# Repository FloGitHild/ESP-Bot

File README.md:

# ESP32-Kettenroboter

Ein modularer Kettenroboter als MINT-Lernprojekt: Schülerinnen und Schüler
sollen Aufbau, Sensorik und Programmierung eines mobilen Roboters kennenlernen.
Das Projekt verbindet ein Robotik-Konzept mit KiCad-Entwürfen und ersten
Arduino-Testprogrammen.

> **Projektstand:** Dieses Repository dokumentiert ein Konzept und begonnene
> Hardware-Entwicklung. Die beschriebenen Funktionen sind nicht automatisch
> als fertig aufgebaut, vollständig programmiert oder praktisch validiert zu
> verstehen. Insbesondere ist hier noch keine vollständige Fahr- und
> Autonomiesoftware enthalten.

## Konzept

Der geplante Roboter soll Hindernisse erkennen, Linien verfolgen, Abstände und
Fahrdaten erfassen und Daten per WLAN weitergeben. Das Konzept sieht vor, bis zu
20 möglichst gleiche Einheiten für den MINT-Unterricht aufzubauen.

Wesentliche Bausteine der beschriebenen Architektur:

- **Zwei Controller:** Ein ESP32-WROOM-32E übernimmt die übergeordnete Logik,
  Sensorik und WLAN-Kommunikation. Ein Arduino Pro Micro ist für zeitkritische
  Motorsteuerung, Encoder und Signaltöne vorgesehen.
- **Kettenantrieb:** Zwei N20-Getriebemotoren mit Encodern werden über einen
  Motortreiber angesteuert.
- **Sensorik:** Ein HC-SR04 für die Hinderniserkennung vorn, zwei VL53L0X für
  seitliche Abstandsmessung, ein TCS34725 für die Linienerkennung und eine
  LSM6DSOX-IMU für Beschleunigungs- und Drehratenmessung.
- **Erweiterbarer I²C-Bus:** Ein TCA/PCA9548A-Multiplexer soll Sensoren mit
  gleicher I²C-Adresse voneinander trennen. Ein zusätzlicher Anschluss am
  Gehäusedeckel ist für externe I²C-Module vorgesehen.
- **Rückmeldung und Aufzeichnung:** OLED, WS2812-LEDs und Piezo dienen der
  Ausgabe; eine microSD-Karte ist für Sensor- und Fahrdaten vorgesehen.
- **Energieversorgung:** Das Konzept beschreibt einen 1S-LiPo-Akku mit
  getrennten Boost-Versorgungen für Motoren und Logik.

Die detaillierte Beschreibung, Pin- und Busbelegungen, Stückliste sowie
Kostenschätzungen stehen in den Konzeptunterlagen. Werte daraus sind
Planungsangaben und müssen vor dem Aufbau anhand der verwendeten Bauteile
überprüft werden.

## Inhalt des Repositorys

| Pfad | Inhalt |
| --- | --- |
| [`Kettenroboter_Konzept_V1.0.html`](Kettenroboter_Konzept_V1.0.html) | Ausführliche Konzeptbeschreibung mit Architektur, Sensorik, Versorgung, Pinplan und Kalkulation |
| [`Kettenroboter_Konzept_V1.0.docx`](Kettenroboter_Konzept_V1.0.docx) | Bearbeitbare Fassung des Konzepts |
| [`Kettenroboter - Konzept V1.0.pdf`](Kettenroboter%20-%20Konzept%20V1.0.pdf) | PDF-Fassung des Konzepts |
| [`KICAD/Platine_V1.0/`](KICAD/Platine_V1.0/) | KiCad-Schaltplan- und Platinenprojekt V1.0 |
| [`Arduino Codes/`](Arduino%20Codes/) | Arduino-Sketche für einzelne Hardwaretests |
| [`Datenblätter/`](Datenbl%C3%A4tter/) | Datenblätter und ESP32-Maßzeichnung |
| [`Teilliste.xlsx`](Teilliste.xlsx) | Bauteil- und Bestellübersicht |
| [`Neue Notiz 09-22-2026.pdf`](Neue%20Notiz%2009-22-2026.pdf) | Zusätzliche Projektnotiz |

## Arduino-Testsketche

Die Sketche testen einzelne Baugruppen und sind kein zusammenhängendes
Roboterprogramm:

| Sketch | Zweck |
| --- | --- |
| [`IIC_Bus_Scanner.ino`](Arduino%20Codes/IIC_Bus_Scanner/IIC_Bus_Scanner.ino) | Sucht I²C-Geräte direkt und an den Kanälen eines Multiplexers |
| [`IIC_MUX_Test.ino`](Arduino%20Codes/IIC_MUX_Test/IIC_MUX_Test.ino) | Prüft Multiplexer, Buspegel und Kanalwahl |
| [`MUX_Test.ino`](Arduino%20Codes/MUX_Test/MUX_Test.ino) | Weiterer Multiplexer-Test |
| [`OLED_Direct_Test.ino`](Arduino%20Codes/OLED_Direct_Test/OLED_Direct_Test.ino) | Initialisiert ein OLED und zeigt Beispieltexte an |

Die Sketche verwenden derzeit SDA an GPIO 15 und SCL an GPIO 16. Im
Konzept-Pinplan ist der I²C-Hauptbus dagegen auf GPIO 21/22 vorgesehen.
Vor dem Anschließen oder Ausführen daher die tatsächliche Verdrahtung, den
jeweiligen Sketch und den passenden ESP32-Pinplan miteinander abgleichen.
Der OLED-Test verwendet die Bibliothek **Adafruit_SSD1306**.

## Sicherheit und Prüfung

Der Entwurf umfasst einen Lithium-Polymer-Akku, Ladeelektronik, DC/DC-Wandler
und Motoren. Vor einem Aufbau oder Ladebetrieb müssen insbesondere Akku,
Ladeschaltung, Schutzfunktionen, Leitungsquerschnitte und Strombelastbarkeit
für die tatsächlich ausgewählten Komponenten geprüft werden. Lithium-Akkus
nicht unbeaufsichtigt oder entgegen den Herstellerangaben laden.

ESP32-GPIOs sind nicht 5-V-tolerant. Für den im Konzept vorgesehenen HC-SR04
muss insbesondere das Echo-Signal auf einen zulässigen ESP32-Pegel angepasst
werden. Maßgeblich sind die Datenblätter der konkret eingesetzten Bauteile.

## Urheberschaft und Nutzung

Die eigenen Projektideen, konzeptionellen Entscheidungen und Ausarbeitungen
dieses Projekts stammen von **Florian (GitHub: [FloGitHild](https://github.com/FloGitHild))**.
Sie dürfen nur verwendet, bearbeitet oder weiterverbreitet werden, wenn
**Florian (FloGitHild) klar als Urheber genannt wird**. Eine Nutzung ohne diese
Namensnennung ist nicht gestattet.

Die Namensnennung ist keine pauschale Lizenz für Inhalte Dritter. Datenblätter,
Herstellerangaben, Produktnamen und sonstige übernommene Materialien
unterliegen weiterhin den Rechten und Bedingungen ihrer jeweiligen
Rechteinhaber. Für solche Inhalte gelten die jeweiligen Lizenz- und
Nutzungsbedingungen.

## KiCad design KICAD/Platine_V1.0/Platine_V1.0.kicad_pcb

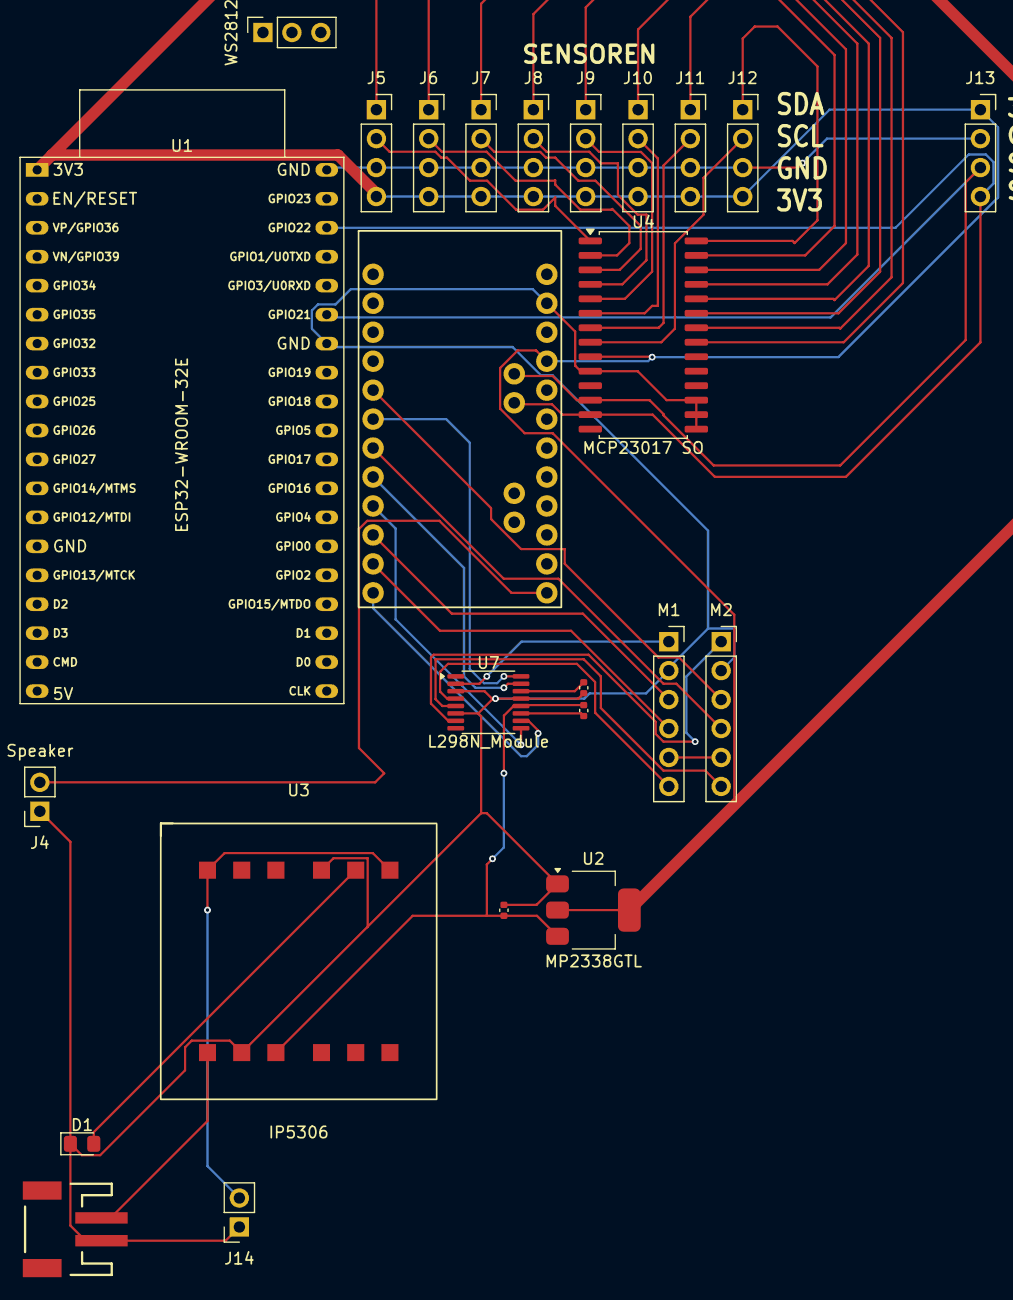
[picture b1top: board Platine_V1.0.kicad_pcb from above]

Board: 2 copper layers, 25 parts (0 on the bottom side), 40 nets.

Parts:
C1: 0.1uF; C_0402_1005Metric
C2: 2.2uF; C_0402_1005Metric
C3: 10uF; C_0402_1005Metric
D1: LED; LED_0805_2012Metric_Pad1.15x1.40mm_HandSolder
J1: JST_2mm_LiPo; JST_1x02_P2.0mm_Horizontal_SMD
J4: Speaker; PinSocket_1x02_P2.54mm_Vertical
J5, J6, J7, J8, J9, J10, J11, J12, J13: Conn_01x04_Socket; PinSocket_1x04_P2.54mm_Vertical
J14: Conn_01x02_Socket; PinSocket_1x02_P2.54mm_Vertical
M1, M2: Conn_01x06_Socket; PinSocket_1x06_P2.54mm_Vertical
U1: ESP32-WROOM-32E
U2: MP2338GTL; MP2338GTL_SOT23-5
U3: IP5306; IP5306_Module
U4: MCP23017 SO; L298N_Module
U5: Arduino Pro Mini; Arduino_Pro_Mini_Shield
U7: L298N_Module
WS2812: Conn_01x03_Socket; PinSocket_1x03_P2.54mm_Vertical

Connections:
unnamed: D1.2 (A), U3.5 (CHRG)
unnamed: C2.1, C3.1, D1.1 (K), J1.1 (-), J4.1, J5.3, J6.3, J7.3, J8.3, J9.3, J10.3, J11.3, J12.3, J13.2, J14.1, M1.2, M2.2, U1.14 (GND), U1.32 (GND), U1.38 (GND), U2.1 (GND), U3.4 (GND), U3.8 (BAT-), U4.10 (V_{SS}), U4.15 (A0), U4.16 (A1), U4.17 (A2), U5.23 (GND), U7.3 (AISEN), U7.6 (BISEN), U7.13 (GND), WS2812.3
unnamed: J1.2 (+), U3.7 (BAT+)
unnamed: M1.1, U7.2 (AOUT1)
unnamed: M1.3, U5.10 (D7)
unnamed: M1.4, U5.11 (D8)
unnamed: M1.5, M2.5
unnamed: M1.6, U7.4 (AOUT2)
unnamed: M2.1, U7.7 (BOUT1)
unnamed: M2.3, U5.5 (D2)
unnamed: M2.4, U5.7 (D4)
unnamed: M2.6, U7.5 (BOUT2)
unnamed: J4.2, U5.13 (~D10)
unnamed: J5.1, U4.21 (GPA0)
unnamed: J5.2, U4.1 (GPB0)
unnamed: J6.1, U4.22 (GPA1)
unnamed: J6.2, U4.2 (GPB1)
unnamed: J7.1, U4.23 (GPA2)
unnamed: J7.2, U4.3 (GPB2)
unnamed: J8.1, U4.24 (GPA3)
unnamed: J8.2, U4.4 (GPB3)
unnamed: J9.1, U4.25 (GPA4)
unnamed: J9.2, U4.5 (GPB4)
unnamed: J10.1, U4.26 (GPA5)
unnamed: J10.2, U4.6 (GPB5)
unnamed: J5.4, J6.4, J7.4, J8.4, J9.4, J10.4, J11.4, J12.4, J13.1, U1.1 (3V3), U2.2 (VO), U4.9 (V_{DD}), U5.21 (VCC)
unnamed: J11.1, U4.27 (GPA6)
unnamed: J11.2, U4.7 (GPB6)
unnamed: J12.1, U4.28 (GPA7)
unnamed: J12.2, U4.8 (GPB7)
unnamed: J13.3, U1.33 (GPIO21), U4.12 (SCK), U5.28 (A5/SCL)
unnamed: J13.4, U1.36 (GPIO22), U4.13 (SDA), U5.27 (A4/SDA)
unnamed: J14.2, U3.1 (VBUS), U3.6 (WAKE)
unnamed: C1.2, C3.2, U1.35 (U0TXD/GPIO1), U2.3 (VI), U3.9 (LOAD), U7.12 (VM), WS2812.1, WS2812.2
unnamed: U5.6 (~D3), U7.16 (AIN1)
unnamed: U5.8 (~D5), U7.15 (AIN2)
unnamed: U5.9 (~D6), U7.9 (BIN1)
unnamed: U5.12 (~D9), U7.10 (BIN2)
unnamed: C1.1, U7.11 (VCP)
unnamed: C2.2, U7.14 (VINT)
